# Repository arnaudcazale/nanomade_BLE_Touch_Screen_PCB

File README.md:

# nanomade_BLE_Touch_Screen_PCB

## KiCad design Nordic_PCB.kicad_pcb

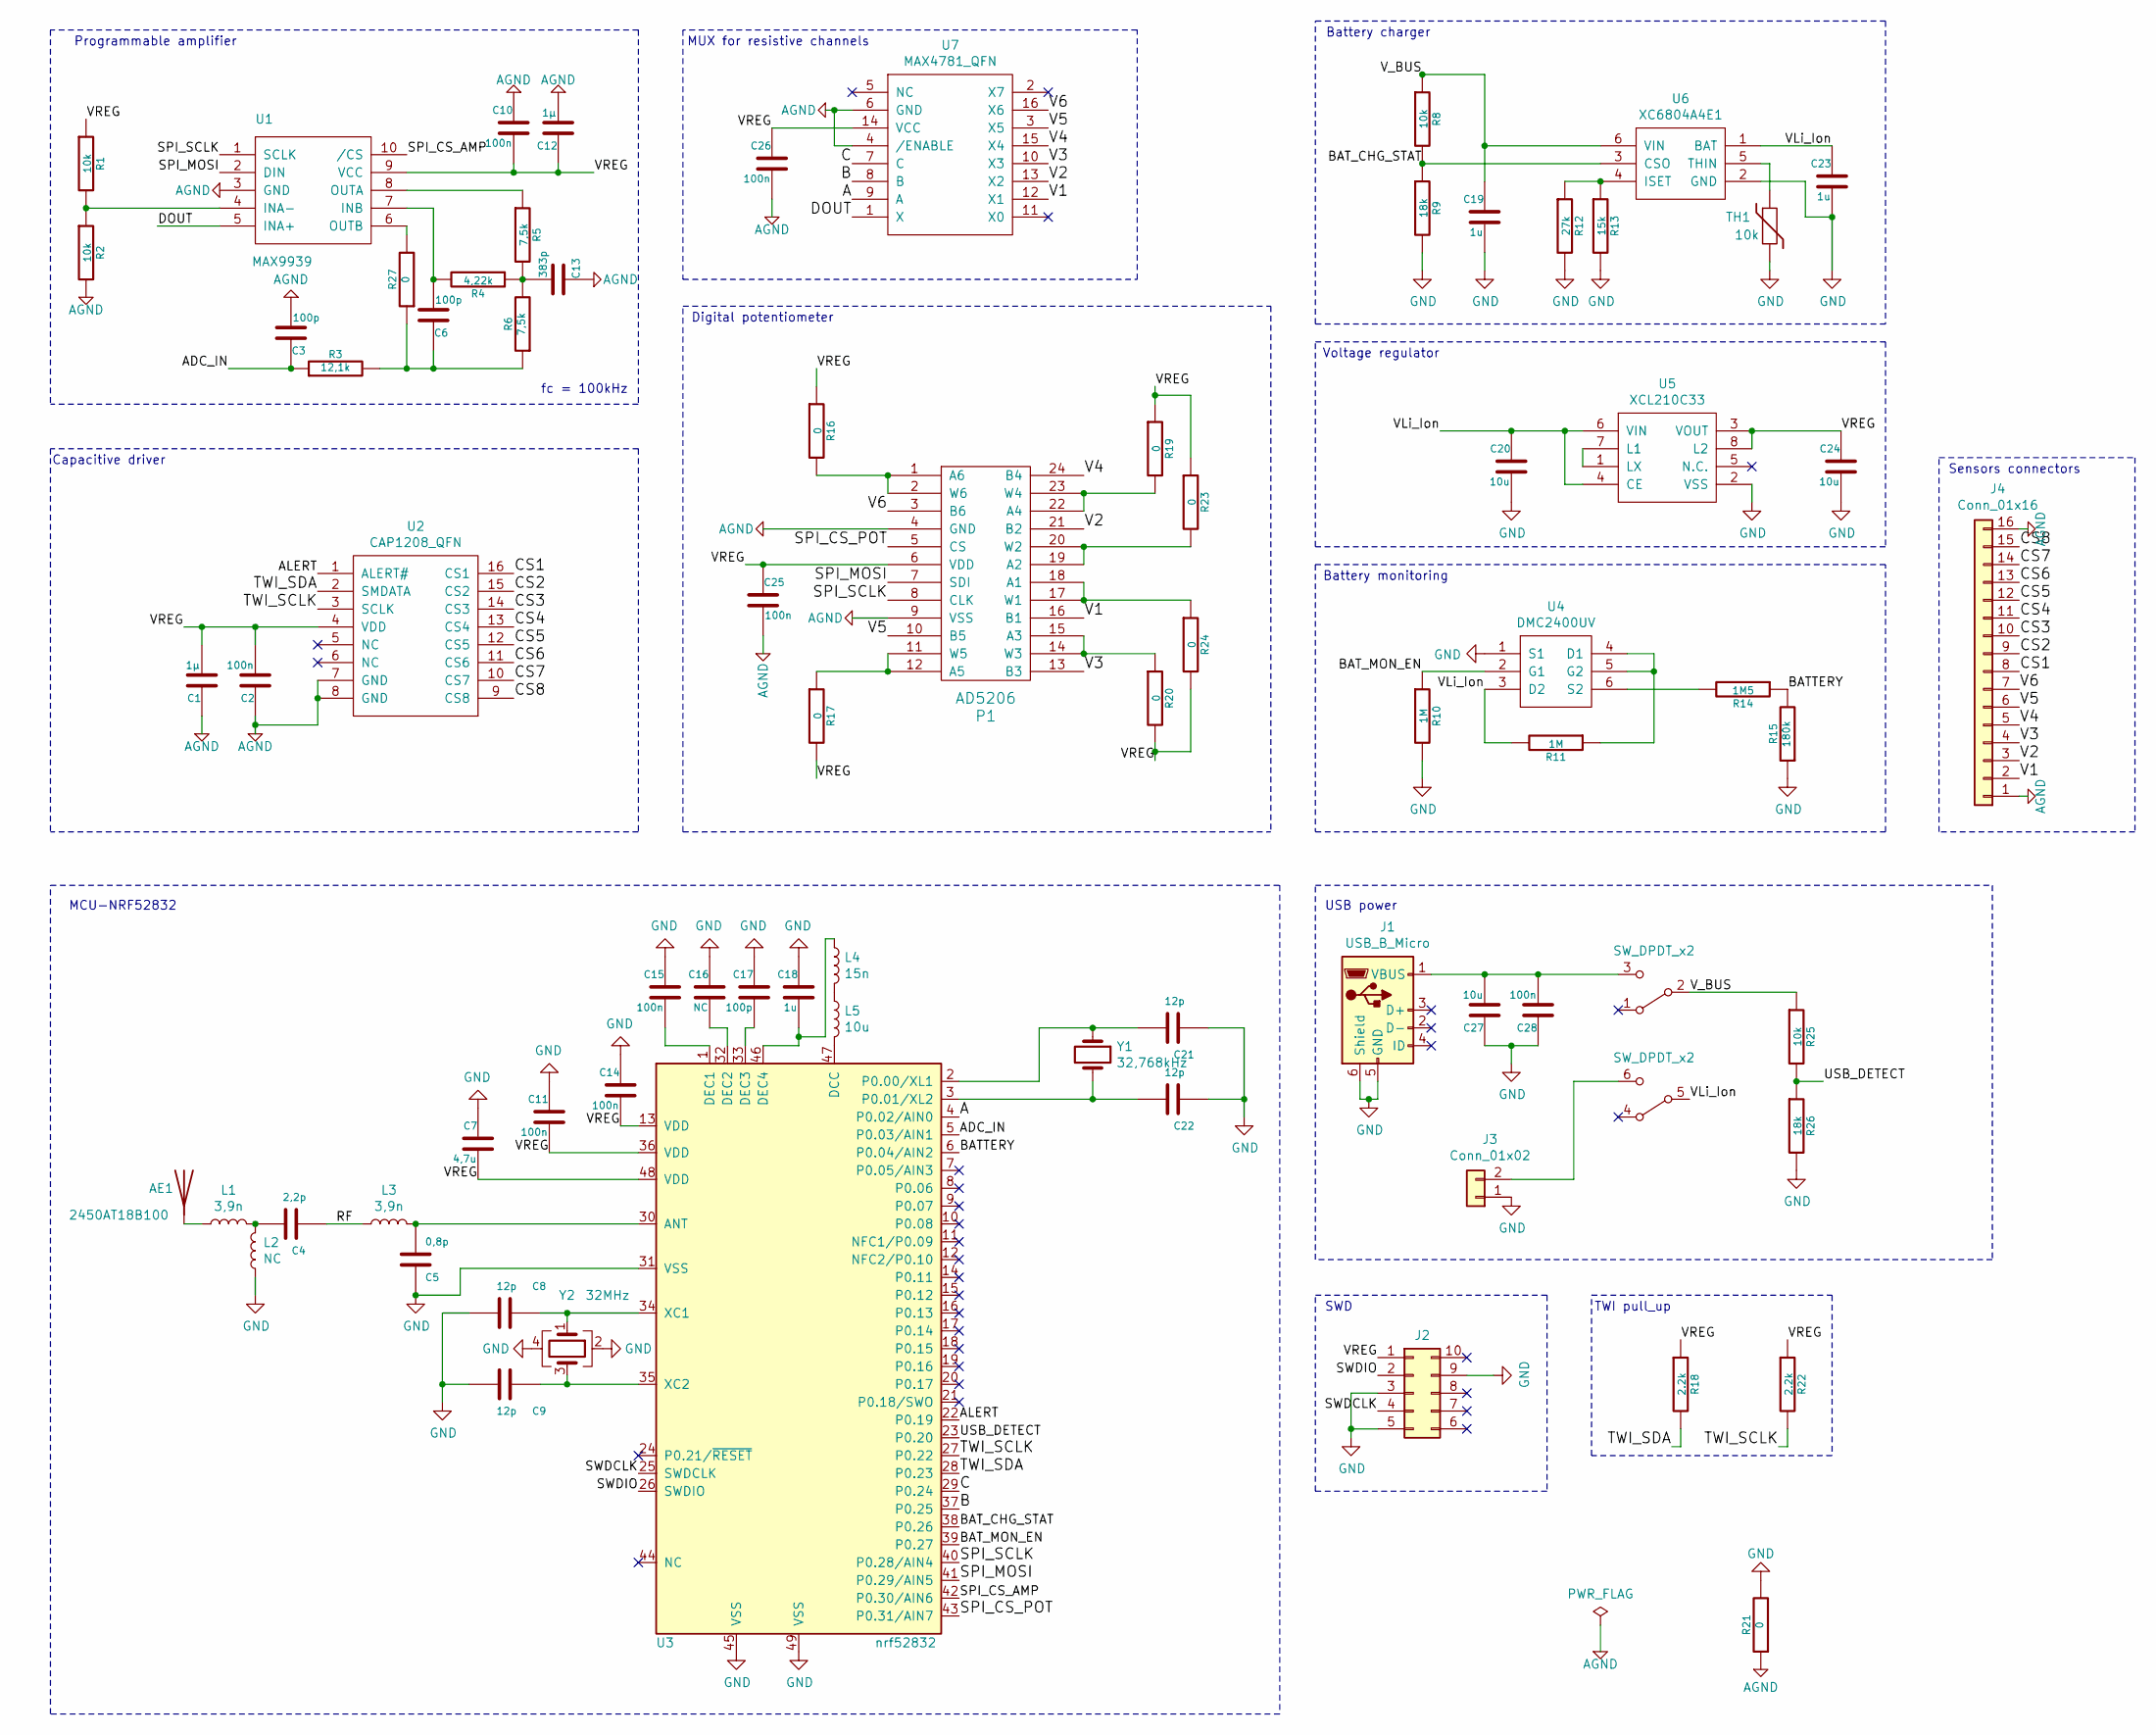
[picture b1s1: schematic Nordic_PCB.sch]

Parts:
AE1: 2450AT18B100
C1, C12: 1µ; C_0603_1608Metric
C2, C10, C11, C14, C15, C25, C26, C28: 100n; C_0402_1005Metric
C3, C6, C17: 100p; C_0402_1005Metric
C4: 2,2p; C_0402_1005Metric
C5: 0,8p; C_0402_1005Metric
C7: 4,7u; C_0603_1608Metric
C8, C9, C21, C22: 12p; C_0402_1005Metric
C13: 383p; C_0402_1005Metric
C16: NC; C_0402_1005Metric
C18, C19, C23: 1u; C_0603_1608Metric
C20, C24, C27: 10u; C_0603_1608Metric
J1: USB_B_Micro; USB_Micro-B_Molex_47346-0001
J2: Conn_02x05_Counter_Clockwise; Tag_Connect_10
J3: Conn_01x02; JST_SH_SM02B-SRSS-TB_02x1.00mm_Angled
J4: Conn_01x16; 117345926
L1, L3: 3,9n; L_0402
L2: NC; L_0402
L4: 15n; L_0402
L5: 10u; L_0603
P1: AD5206; TSSOP-24_4.4x7.8mm_Pitch0.65mm
R1, R2, R8, R25: 10k; R_0402_1005Metric
R3: 12,1k; R_0402_1005Metric
R4: 4,22k; R_0402_1005Metric
R5, R6: 7,5k; R_0402_1005Metric
R9, R26: 18k; R_0402_1005Metric
R10, R11: 1M; R_0402_1005Metric
R12: 27k; R_0402_1005Metric
R13: 15k; R_0402_1005Metric
R14: 1M5; R_0402_1005Metric
R15: 180k; R_0402_1005Metric
R16, R17, R19, R20, R21, R23, R24, R27: 0; R_0402_1005Metric
R18, R22: 2.2k; R_0402_1005Metric
SW1: SW_DPDT_x2; JS202011JCQN-DPDT
TH1: 10k; R_0402_1005Metric
U1: MAX9939; MSOP-10_3x3mm_Pitch0.5mm
U2: CAP1208_QFN; QFN-16-1EP_3x3mm_Pitch0.5mm_ThermalVias
U3: nrf52832; QFN-48-1EP_6x6mm_Pitch0.4mm_ThermalVias
U4: DMC2400UV; SOT-563
U5: XCL210C33; CL-2025-02
U6: XC6804A4E1; USP-6EL
U7: MAX4781_QFN; QFN-16-1EP_3x3mm_Pitch0.5mm
Y1: 32,768kHz; Crystal_SMD_2012-2pin_2.0x1.2mm
Y2: 32MHz; Crystal_SMD_2016-4pin_2.0x1.6mm

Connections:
/A: U3.4 (P0.02/AIN0), U7.9 (A)
/ADC_IN: C3.1, R3.1, U3.5 (P0.03/AIN1)
/ALERT: U2.1 (ALERT#), U3.22 (P0.19)
/B: U3.37 (P0.25), U7.8 (B)
/BATTERY: R14.1, R15.2, U3.6 (P0.04/AIN2)
/BAT_CHG_STAT: R8.2, R9.1, U3.38 (P0.26), U6.3 (CSO)
/BAT_MON_EN: R10.1, U3.39 (P0.27), U4.2 (G1)
/C: U3.29 (P0.24), U7.7 (C)
/CS1: J4.8, U2.16 (CS1)
/CS2: J4.9, U2.15 (CS2)
/CS3: J4.10, U2.14 (CS3)
/CS4: J4.11, U2.13 (CS4)
/CS5: J4.12, U2.12 (CS5)
/CS6: J4.13, U2.11 (CS6)
/CS7: J4.14, U2.10 (CS7)
/CS8: J4.15, U2.9 (CS8)
/DOUT: U1.5 (INA+), U7.1 (X)
/RF: C4.1, L3.1; also elsewhere on the board
/SPI_CS_AMP: U1.10 (/CS), U3.42 (P0.30/AIN6)
/SPI_CS_POT: P1.5 (CS), U3.43 (P0.31/AIN7)
/SPI_MOSI: P1.7 (SDI), U1.2 (DIN), U3.41 (P0.29/AIN5)
/SPI_SCLK: P1.8 (CLK), U1.1 (SCLK), U3.40 (P0.28/AIN4)
/SWDCLK: J2.4, U3.25 (SWDCLK)
/SWDIO: J2.2, U3.26 (SWDIO)
/TWI_SCLK: R22.2, U2.3 (SCLK), U3.27 (P0.22)
/TWI_SDA: R18.2, U2.2 (SMDATA), U3.28 (P0.23)
/USB_DETECT: R25.2, R26.1, U3.23 (P0.20)
/V1: J4.2, P1.16 (B1), U7.12 (X1)
/V2: J4.3, P1.21 (B2), U7.13 (X2)
/V3: J4.4, P1.13 (B3), U7.10 (X3)
/V4: J4.5, P1.24 (B4), U7.15 (X4)
/V5: J4.6, P1.10 (B5), U7.3 (X5)
/V6: J4.7, P1.3 (B6), U7.16 (X6)
/VLi_Ion: C20.1, C23.1, R11.2, SW1.5 (B), U4.3 (D2), U5.4 (CE), U5.6 (VIN), U6.1 (BAT)
/VREG: C1.2, C2.2, C7.2, C10.2, C11.2, C12.1, C14.2, C24.1, C25.1, C26.1, J2.1, P1.6 (VDD), R1.1, R16.1, R17.2, R18.1, R19.1, R20.2, R22.1, R23.1, R24.2, U1.9 (VCC), U2.4 (VDD), U3.13 (VDD), U3.36 (VDD), U3.48 (VDD), U5.3 (VOUT), U5.8 (L2), U7.14 (VCC)
/V_BUS: C19.1, R8.1, R25.1, SW1.2 (B), U6.6 (VIN)
AGND: C1.1, C2.1, C3.2, C10.1, C12.2, C13.1, C25.2, C26.2, J4.1, J4.16, P1.4 (GND), P1.9 (VSS), R2.2, R21.1, U1.3 (GND), U2.7 (GND), U2.8 (GND), U7.4 (/ENABLE), U7.6 (GND)
GND: C5.1, C7.1, C8.2, C9.2, C11.1, C14.1, C15.1, C16.1, C17.1, C18.1, C19.2, C20.2, C21.1, C22.1, C23.2, C24.2, C27.1, C28.1, J1.5 (GND), J1.6 (Shield), J2.3, J2.5, J2.9, J3.1, L2.1, R9.2, R10.2, R12.2, R13.2, R15.1, R21.2, R26.2, TH1.2, U3.31 (VSS), U3.45 (VSS), U3.49 (VSS), U4.1 (S1), U5.2 (VSS), U6.2 (GND), Y2.2, Y2.4
unnamed: AE1.1, L1.1
unnamed: C4.2, L1.2, L2.2
unnamed: C5.2, L3.2, U3.30 (ANT)
unnamed: C6.1, R3.2, R6.1, R27.1
unnamed: C6.2, R4.2, U1.7 (INB)
unnamed: C8.1, U3.34 (XC1), Y2.1
unnamed: C9.1, U3.35 (XC2), Y2.3
unnamed: C13.2, R4.1, R5.2, R6.2
unnamed: C15.2, U3.1 (DEC1)
unnamed: C16.2, U3.32 (DEC2)
unnamed: C17.2, U3.33 (DEC3)
unnamed: C18.2, L4.1, U3.46 (DEC4)
unnamed: C21.2, U3.2 (P0.00/XL1), Y1.1
unnamed: C22.2, U3.3 (P0.01/XL2), Y1.2
unnamed: C27.2, C28.2, J1.1 (VBUS), SW1.3 (C)
unnamed: J3.2, SW1.6 (C)
unnamed: L4.2, L5.1
unnamed: L5.2, U3.47 (DCC)
unnamed: P1.1 (A6), P1.2 (W6), R16.2
unnamed: P1.11 (W5), P1.12 (A5), R17.1
unnamed: P1.14 (W3), P1.15 (A3), R20.1
unnamed: P1.17 (W1), P1.18 (A1), R24.1
unnamed: P1.19 (A2), P1.20 (W2), R23.2
unnamed: P1.22 (A4), P1.23 (W4), R19.2
unnamed: R1.2, R2.1, U1.4 (INA-)
unnamed: R5.1, U1.8 (OUTA)
unnamed: R11.1, U4.4 (D1), U4.5 (G2)
unnamed: R12.1, R13.1, U6.4 (ISET)
unnamed: R14.2, U4.6 (S2)
unnamed: R27.2, U1.6 (OUTB)
unnamed: TH1.1, U6.5 (THIN)
unnamed: U5.1 (LX), U5.7 (L1)

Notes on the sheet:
Capacitive driver
Digital potentiometer
MUX for resistive channels
Programmable amplifier
Battery charger
Voltage regulator
Battery monitoring
TWI pull_up
MCU-NRF52832
USB power
SWD
Sensors connectors
fc = 100kHz

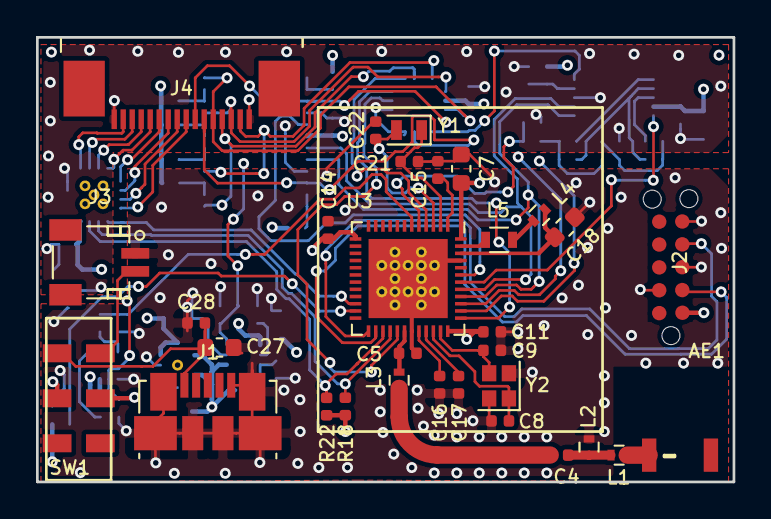
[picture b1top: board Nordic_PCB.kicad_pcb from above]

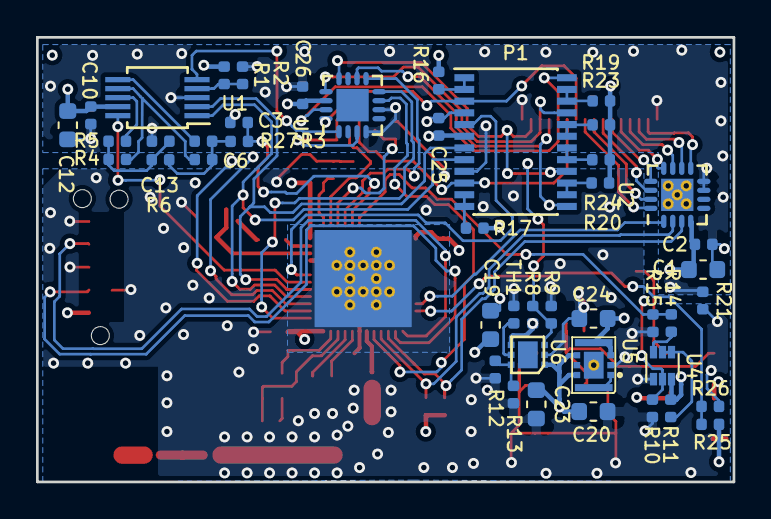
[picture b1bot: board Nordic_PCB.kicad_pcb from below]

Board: 4 copper layers, 38.7 x 24.7 mm, 77 parts (45 on the bottom side), 70 nets.

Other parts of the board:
uwA*****: uwArc0.96_2.12_90

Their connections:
/RF: uwA*****.1; also elsewhere on the board

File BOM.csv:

Id;Référence;Boîtier;Quantité;Désignation;Fournisseur et réf
1;uwA*****;uwArc0.96_2.12_90;1;uwArc0.96_2.12_90;
2;AE1;2450AT18B100;1;2450AT18B100;
3;C1,C12;C_0603_1608Metric;2;1µ;
4;C2,C10,C11,C14,C15,C25,C26,C28;C_0402_1005Metric;8;100n;
5;C3,C6,C17;C_0402_1005Metric;3;100p;
6;C4;C_0402_1005Metric;1;2,2p;
7;C5;C_0402_1005Metric;1;0,8p;
8;C8,C9,C21,C22;C_0402_1005Metric;4;12p;
9;C13;C_0402_1005Metric;1;383p;
10;C16;C_0402_1005Metric;1;NC;
11;C19,C23,C18;C_0603_1608Metric;3;1u;
12;C20,C24,C27;C_0603_1608Metric;3;10u;
13;J1;USB_Micro-B_Molex_47346-0001;1;USB_B_Micro;
14;J2;Tag_Connect_10;1;Conn_02x05_Counter_Clockwise;
15;J3;JST_SH_SM02B-SRSS-TB_02x1.00mm_Angled;1;Conn_01x02;
16;J4;117345926;1;Conn_01x16;
17;L1,L3;L_0402;2;3,9n;
18;L2;L_0402;1;NC;
19;L4;L_0402;1;15n;
20;L5;L_0603;1;10u;
21;P1;TSSOP-24_4.4x7.8mm_Pitch0.65mm;1;AD5206;
22;R1,R2,R8,R25,TH1;R_0402_1005Metric;5;10k;
23;R3;R_0402_1005Metric;1;12,1k;
24;R4;R_0402_1005Metric;1;4,22k;
25;R5,R6;R_0402_1005Metric;2;7,5k;
26;R9,R26;R_0402_1005Metric;2;18k;
27;R10,R11;R_0402_1005Metric;2;1M;
28;R12;R_0402_1005Metric;1;27k;
29;R13;R_0402_1005Metric;1;15k;
30;R14;R_0402_1005Metric;1;1M5;
31;R15;R_0402_1005Metric;1;180k;
32;R16,R17,R19,R20,R21,R23,R24,R27;R_0402_1005Metric;8;0;
33;R18,R22;R_0402_1005Metric;2;2.2k;
34;SW1;JS202011JCQN-DPDT;1;SW_DPDT_x2;
35;U1;MSOP-10_3x3mm_Pitch0.5mm;1;MAX9939;
36;U2;QFN-16-1EP_3x3mm_Pitch0.5mm_ThermalVias;1;CAP1208_QFN;
37;U3;QFN-48-1EP_6x6mm_Pitch0.4mm_ThermalVias;1;nrf52832;
38;U4;SOT-563;1;DMC2400UV;
39;U5;CL-2025-02;1;XCL210C33;
40;U6;USP-6EL;1;XC6804A4E1;
41;U7;QFN-16-1EP_3x3mm_Pitch0.5mm;1;MAX4781_QFN;
42;Y1;Crystal_SMD_2012-2pin_2.0x1.2mm;1;32,768kHz;
43;Y2;Crystal_SMD_2016-4pin_2.0x1.6mm;1;32MHz;
44;C7;C_0603_1608Metric;1;4,7u;

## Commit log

2020-05-04 Design checker OK
2020-05-07 BOM added
